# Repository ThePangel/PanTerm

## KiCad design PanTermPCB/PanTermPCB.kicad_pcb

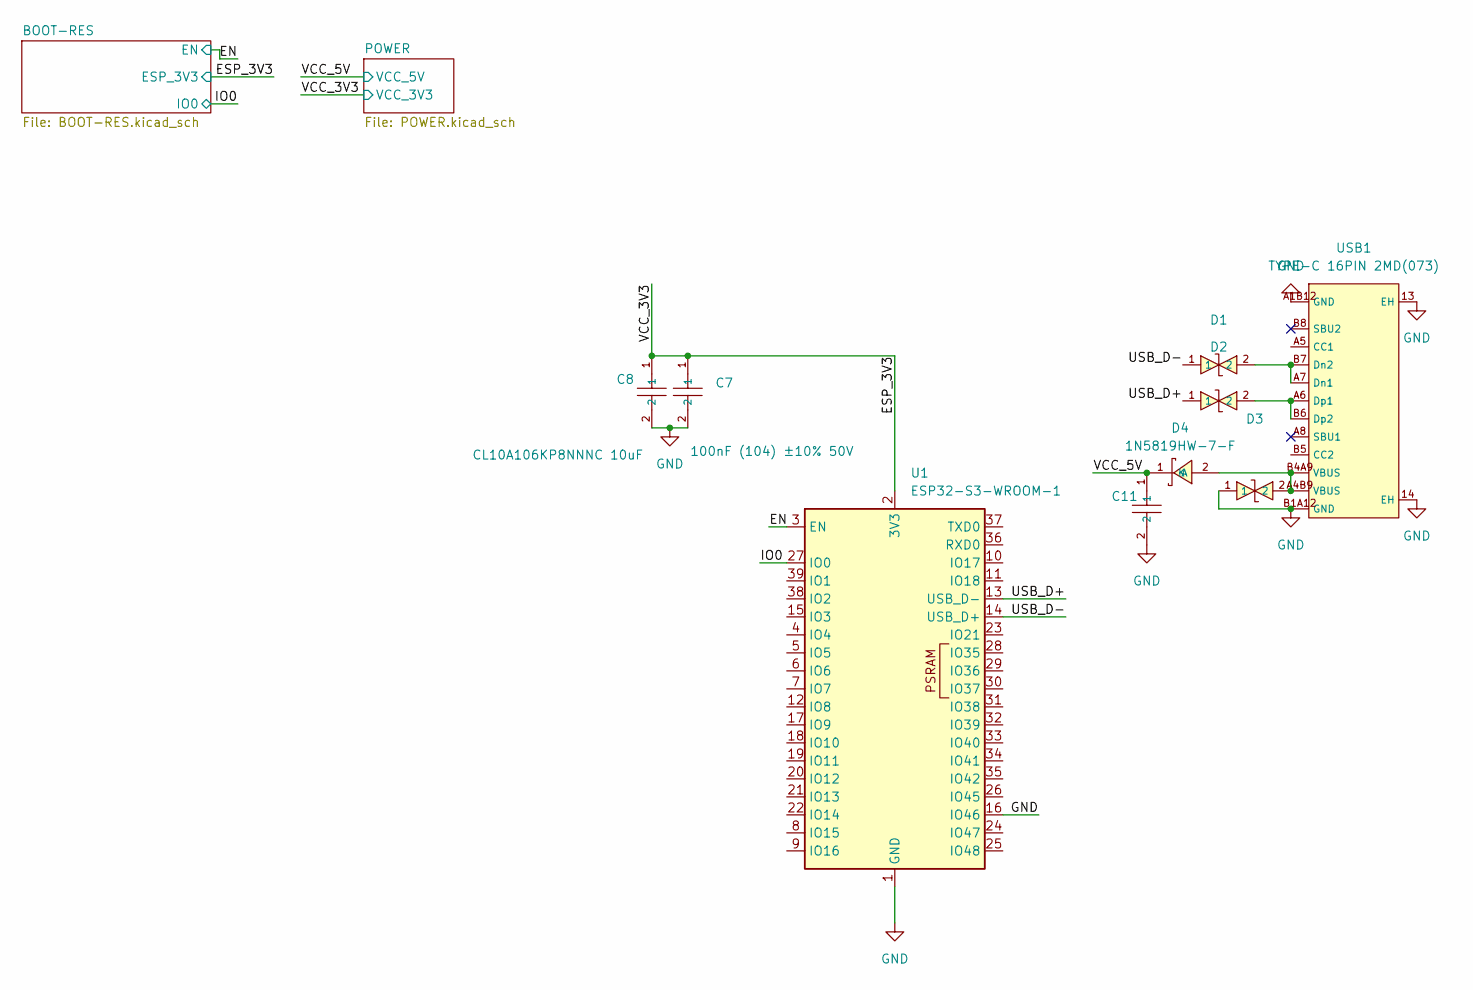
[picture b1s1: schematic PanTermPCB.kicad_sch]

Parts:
C7: 100nF (104) ±10% 50V; C1591_C0603; LCSC C1591
C8, C11: CL10A106KP8NNNC 10uF; C19702_C0603; LCSC C19702
D1, D2, D3: LESD5D5.0CT1G_C41399463; C41399463_SOD-523_L1_2-W0_8-LS1_6-BI; LCSC C41399463
D4: 1N5819HW-7-F; C82544_SOD-123_L2_7-W1_6-LS3_7-RD; LCSC C82544
U1: ESP32-S3-WROOM-1
USB1: TYPE-C 16PIN 2MD(073); C2765186_USB-C-SMD_TYPE-C-16PIN-2MD-073; LCSC C2765186

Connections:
/EN: U1.3 (EN); also elsewhere on the board
/ESP_3V3: C7.1, C8.1, U1.2 (3V3); also elsewhere on the board
/IO0: U1.27 (IO0); also elsewhere on the board
/USB_D+: D2.1, U1.13 (USB_D-)
/USB_D-: D1.1, U1.14 (USB_D+)
/VCC_5V: C11.1, D4.1 (K); also elsewhere on the board
GND: C7.2, C8.2, C11.2, D3.1, U1.1 (GND), U1.16 (IO46), U1.40 (GND), U1.41 (GND), USB1.13 (EH), USB1.14 (EH), USB1.A1B12 (GND), USB1.B1A12 (GND); also elsewhere on the board
unnamed: D3.2, D4.2 (A), USB1.A4B9 (VBUS), USB1.B4A9 (VBUS)
unnamed: D1.2, USB1.A7 (Dn1), USB1.B7 (Dn2)
unnamed: D2.2, USB1.A6 (Dp1), USB1.B6 (Dp2)

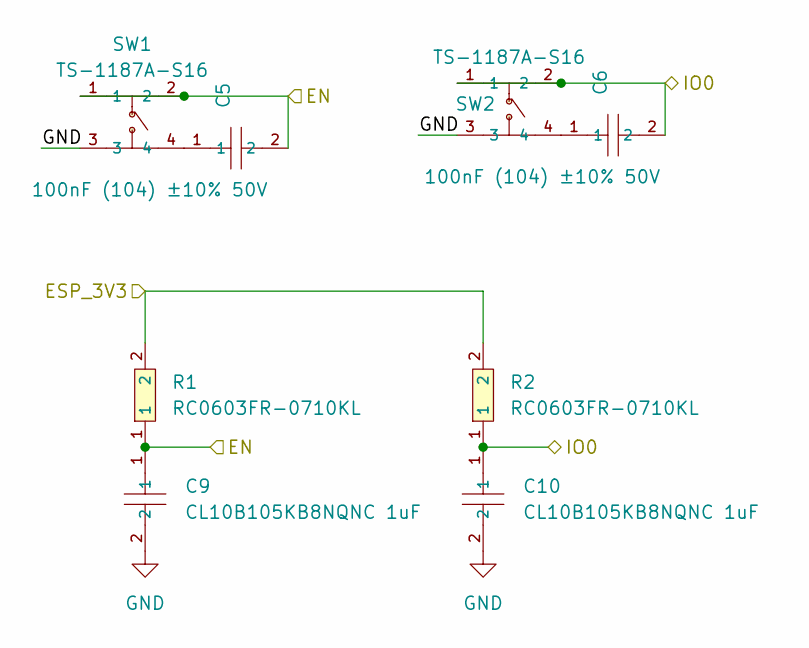
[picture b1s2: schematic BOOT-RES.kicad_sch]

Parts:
C5, C6: 100nF (104) ±10% 50V; C1591_C0603; LCSC C1591
C9, C10: CL10B105KB8NQNC 1uF; C5199872_C0603; LCSC C5199872
R1, R2: RC0603FR-0710KL; C98220_R0603; LCSC C98220
SW1, SW2: TS-1187A-S16; C42420254_SW-SMD_4P-L5_2-W5_2-P3_70-LS6_4; LCSC C42420254

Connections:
/EN: C5.2, C9.1, R1.1, SW1.1, SW1.2; also elsewhere on the board
/ESP_3V3: R1.2, R2.2; also elsewhere on the board
/IO0: C6.2, C10.1, R2.1, SW2.1, SW2.2; also elsewhere on the board
GND: C9.2, C10.2, SW1.3, SW2.3; also elsewhere on the board
unnamed: C5.1, SW1.4
unnamed: C6.1, SW2.4

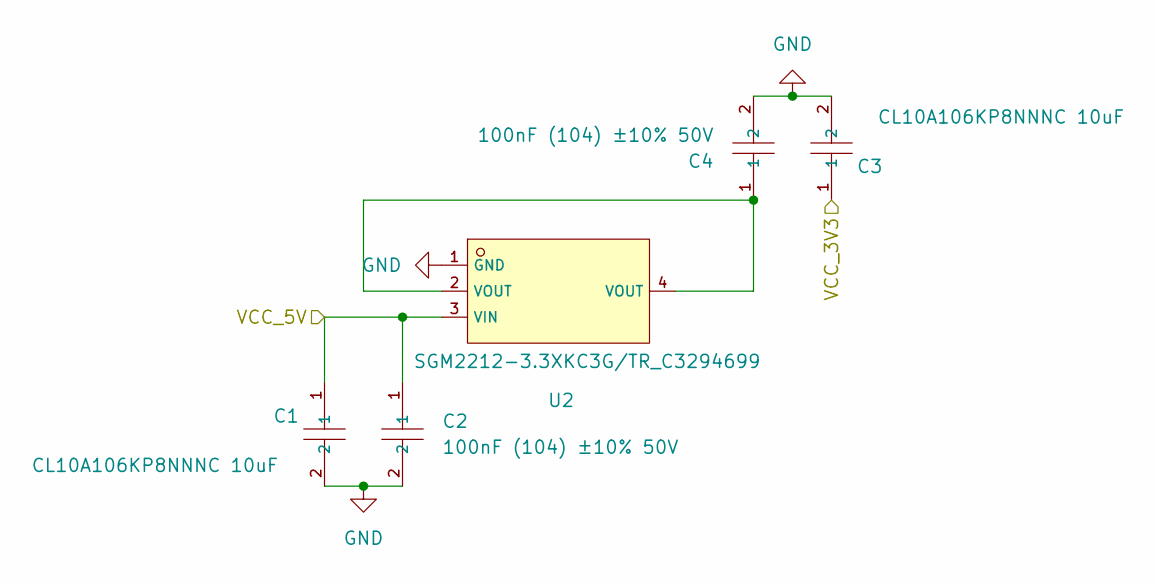
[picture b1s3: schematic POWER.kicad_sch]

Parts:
C1, C3: CL10A106KP8NNNC 10uF; C19702_C0603; LCSC C19702
C2, C4: 100nF (104) ±10% 50V; C1591_C0603; LCSC C1591
U2: SGM2212-3.3XKC3G/TR_C3294699; C3294699_SOT-223-3_L6_5-W3_4-P2_30-LS7_0-BR; LCSC C3294699

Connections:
/ESP_3V3: C3.1; also elsewhere on the board
/VCC_5V: C1.1, C2.1, U2.3 (VIN); also elsewhere on the board
GND: C1.2, C2.2, C3.2, C4.2, U2.1 (GND); also elsewhere on the board
unnamed: C4.1, U2.2 (VOUT), U2.4 (VOUT)

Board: 2 copper layers, 22 parts (0 on the bottom side), 13 nets, no tracks yet.
